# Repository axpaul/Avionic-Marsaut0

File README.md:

# Avionic Marsaut 0

> *© 2021 Paul Miailhe, all rights reserved.*  
> *Material licensed under [→ CC BY-NC-SA 4.0](https://creativecommons.org/licenses/by-nc-sa/4.0)*

## Experimental Rocket Avionics for Marsaut 0

The **Marsaut 0 avionics system**, designed and developed by Paul Miailhe in 2021, was successfully launched during the C'Space event. This project is licensed under **CC BY-NC-SA 4.0**.

The avionics system is based on an **STM32F303K8** microcontroller, which provides high-performance real-time control for the rocket's systems. It integrates essential sensors, motor drivers, and interface boards to ensure a robust and reliable solution for experimental rocketry.

You can access the CAD designs for all the boards [here on GrabCAD](https://grabcad.com/library/avionics-system-for-marsaut-0-rocket-mines-space-1).

---

## System Overview

The electronic architecture of the rocket is divided into the following branches:

---

- **Branch APU** (Acquisition Process Unit):  
  Responsible for acquiring, storing, and transmitting data, equipped with:  
  - **MPU6050**: A 6-axis gyroscope and accelerometer for attitude measurement.  
  - **BMP280**: A barometric pressure sensor for altitude estimation.

---

- **Branch SEQ** (Flight Controller):  
  The core control board, based on the **STM32F303K8**, which manages actuators and flight status monitoring.

---

- **Branch ALIM** (Power Supply):  
  Handles power distribution and monitors the battery's state of charge.

---

- **Branch MOTOR**:  
  Includes two **VNH5019 motor drivers** (by STMicroelectronics) for controlling the parachute deployment system.

---

- **Branch LINK**:  
  Connects all actuators and sensors in the rocket to the avionics for seamless operation.

---

- **Branch HMI** (Human-Machine Interface):  
  Provides a user interface for controlling the system and displaying key information.

---

- **Branch INT_LTS**:  
  Serves as the interface for integrating the **LoRa TTGO-T BEAM** communication module.

---

## Key Components

### **Microcontroller**
- **STM32F303K8**:  
  - ARM Cortex-M3 core with floating-point unit (FPU).  
  - Provides real-time control and data processing capabilities.

### **Sensors**
- **MPU6050**:  
  - A 6-axis IMU for measuring acceleration and angular velocity.  
  - Enables precise attitude and motion tracking.
- **BMP280**:  
  - A barometric pressure sensor for accurate altitude estimation.

### **Motor Drivers**
- **VNH5019** (by STMicroelectronics):  
  - High-power motor drivers capable of handling currents up to 12A.  
  - Used to control the parachute deployment mechanism with precision.

---

## Features and Applications

- **Real-time Control**:  
  The STM32F303K8 ensures smooth operation of actuators and sensors.  

- **Integrated Sensors**:  
  MPU6050 and BMP280 provide reliable data for navigation and altitude tracking.

- **High-Performance Motor Control**:  
  The VNH5019 motor drivers ensure precise parachute deployment and safety.

- **Seamless Communication**:  
  LoRa TTGO-T BEAM module enables efficient data transmission to ground stations.

---

## Visual Overview

### Avionics System CAD
You can find the full CAD designs of the avionics system on [GrabCAD](https://grabcad.com/library/avionics-system-for-marsaut-0-rocket-mines-space-1).

### Images

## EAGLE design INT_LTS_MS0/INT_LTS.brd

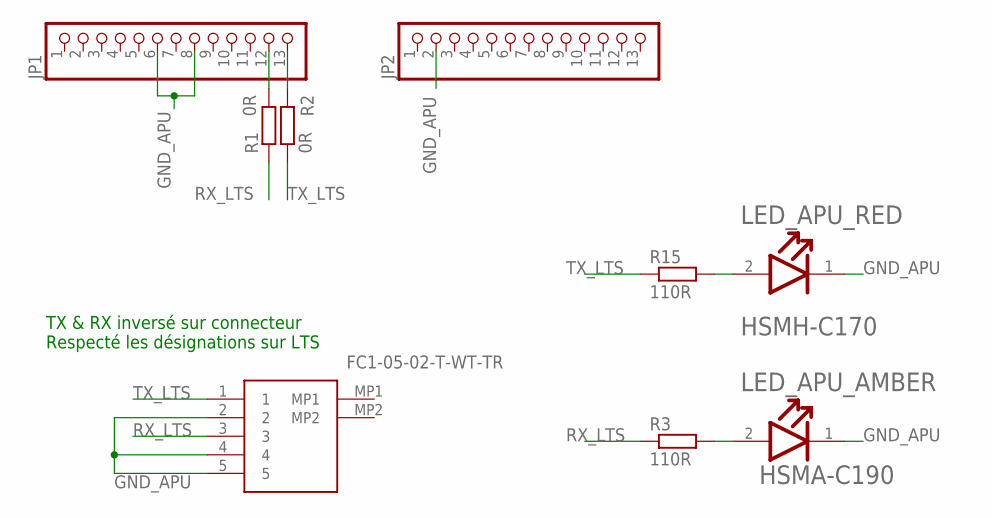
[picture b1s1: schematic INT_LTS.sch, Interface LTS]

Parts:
J7: FC1-05-02-T-WT-TR; FC10502TWTTR
JP1, JP2: PINHD-1X13; 1X13
LED_APU_AMBER: BROADCOM_HSMA-C190BROADCOM_HSMA-C190_0_0; BROADCOM_HSMA-C190_0
LED_APU_RED: BROADCOM_HSMH-C170BROADCOM_HSMH-C170_0_0; BROADCOM_HSMH-C170_0
R1, R2: 0R; R0603
R3, R15: 110R; R0603

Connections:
GND_APU: J7.2, J7.4, J7.5, JP1.6, JP1.8, JP2.2, LED_APU_AMBER.1 (CATHODE), LED_APU_RED.1 (CATHODE)
unnamed: JP1.12, R1.2
unnamed: JP1.13, R2.2
unnamed: LED_APU_AMBER.2 (ANODE), R3.2
unnamed: LED_APU_RED.2 (ANODE), R15.2
RX_LTS: J7.3, R1.1, R3.1
TX_LTS: J7.1, R2.1, R15.1

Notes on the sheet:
TX & RX inversé sur connecteur Respecté les désignations sur LTS

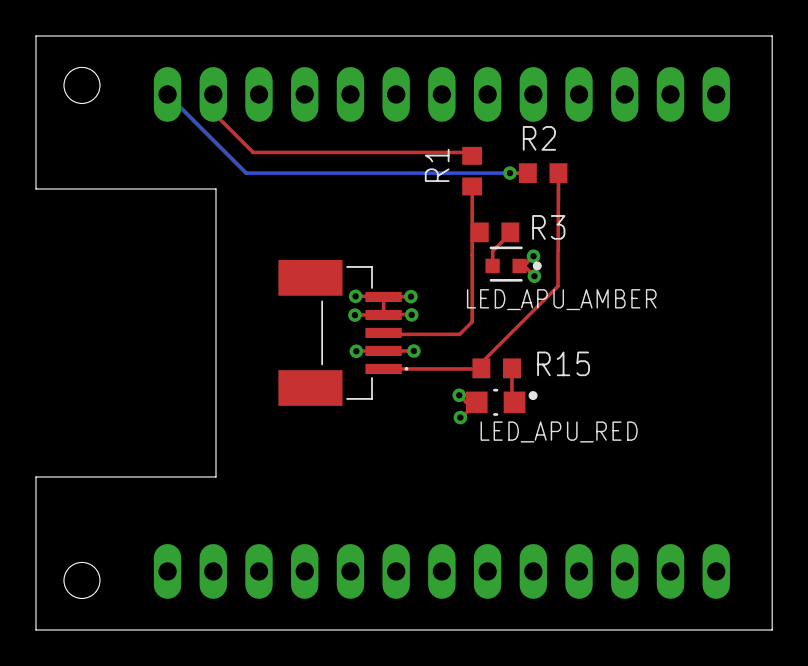
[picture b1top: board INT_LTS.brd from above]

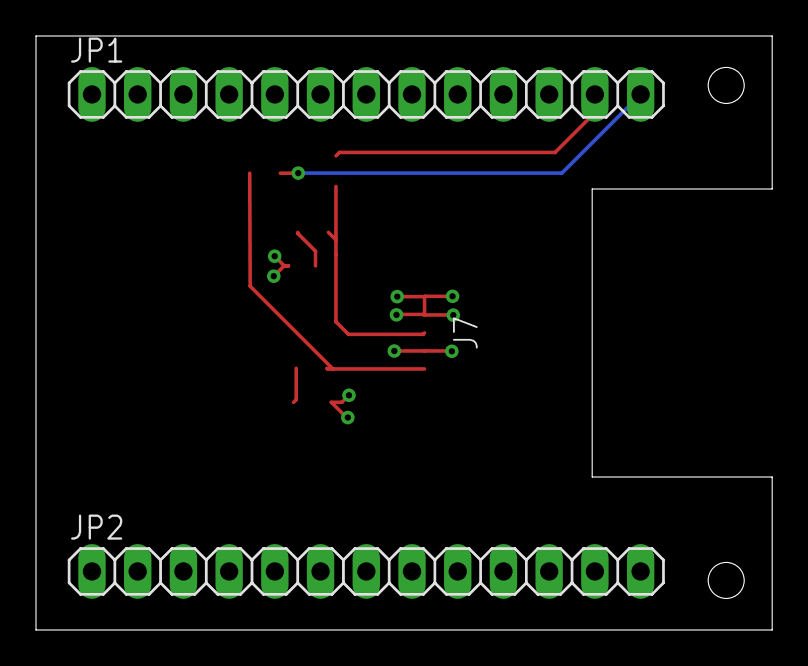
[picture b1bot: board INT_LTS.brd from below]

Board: 2 copper layers, 40.9 x 33.0 mm, 9 parts (2 on the bottom side), 7 nets.

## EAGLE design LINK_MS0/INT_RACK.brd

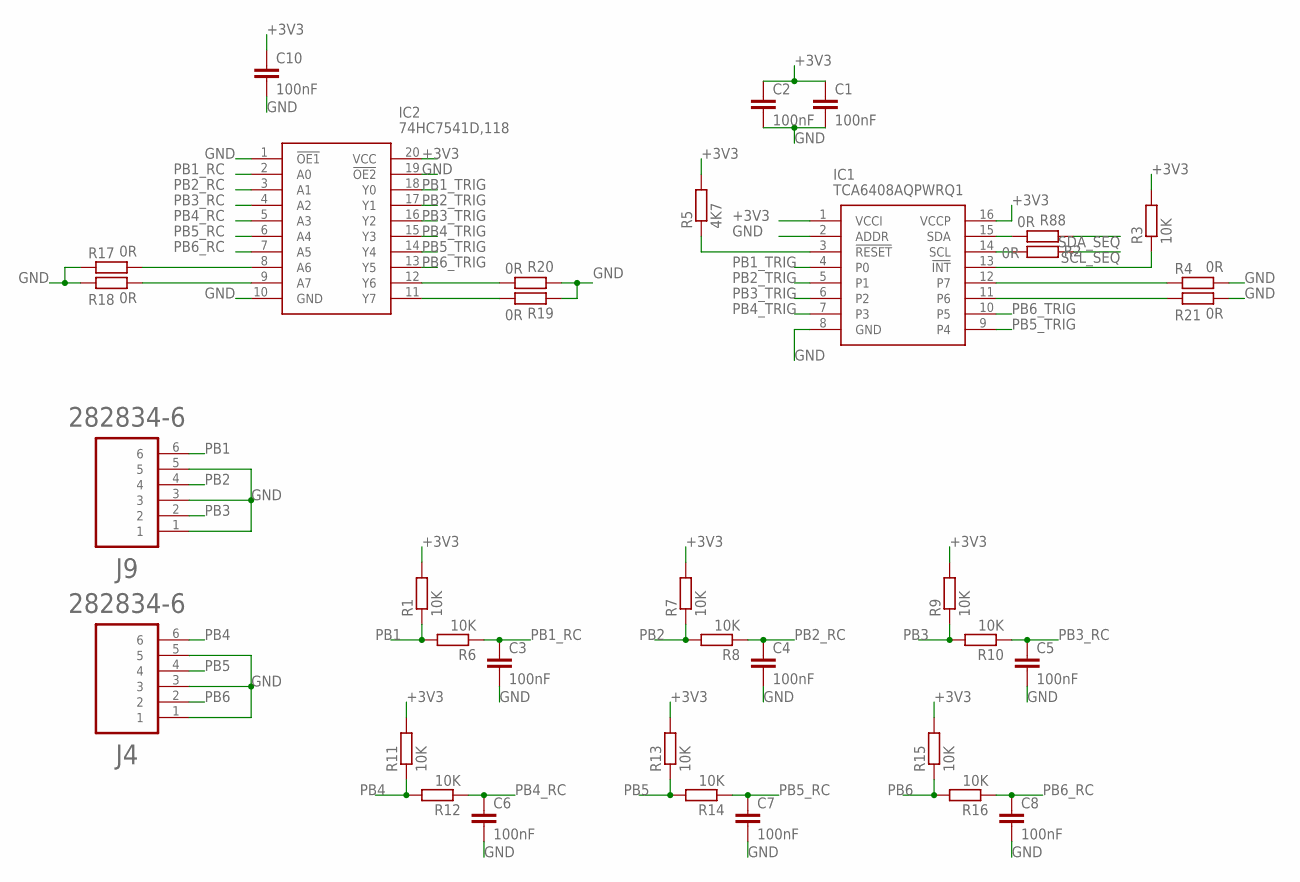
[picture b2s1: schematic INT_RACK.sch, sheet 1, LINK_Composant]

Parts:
C1, C2, C3, C4, C5, C6, C7, C8, C10: 100nF; C0805
IC1: TCA6408AQPWRQ1; SOP65P640X120-16N
IC2: 74HC7541D,118; SOIC127P1032X265-20N
J4, J9: 282834-6; TE_282834-6
R1, R3, R6, R7, R8, R9, R10, R11, R12, R13, R14, R15, R16: 10K; R0603
R2, R4, R17, R18, R19, R20, R21, R88: 0R; R0603
R5: 4K7; R0603

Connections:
+3V3: C1.1, C2.1, C10.1, IC1.1 (VCCI), IC1.16 (VCCP), IC2.20 (VCC), R1.2, R3.2, R5.2, R7.2, R9.2, R11.2, R13.2, R15.2; also elsewhere on the board
GND: C1.2, C2.2, C3.2, C4.2, C5.2, C6.2, C7.2, C8.2, C10.2, IC1.2 (ADDR), IC1.8 (GND), IC2.1 (!OE1), IC2.10 (GND), IC2.19 (!OE2), J4.1, J4.3, J4.5, J9.1, J9.3, J9.5, R4.2, R17.1, R18.1, R19.1, R20.1, R21.2; also elsewhere on the board
unnamed: IC1.11 (P6), R21.1
unnamed: IC1.14 (SCL), R2.2
unnamed: IC1.13 (!INT), R3.1
unnamed: IC1.12 (P7), R4.1
unnamed: IC1.3 (!RESET), R5.1
unnamed: IC2.12 (Y6), R20.2
unnamed: IC2.11 (Y7), R19.2
unnamed: IC2.8 (A6), R17.2
unnamed: IC2.9 (A7), R18.2
unnamed: IC1.15 (SDA), R88.2
PB1: J9.6, R1.1, R6.2
PB1_RC: C3.1, IC2.2 (A0), R6.1
PB1_TRIG: IC1.4 (P0), IC2.18 (Y0)
PB2: J9.4, R7.1, R8.2
PB2_RC: C4.1, IC2.3 (A1), R8.1
PB2_TRIG: IC1.5 (P1), IC2.17 (Y1)
PB3: J9.2, R9.1, R10.2
PB3_RC: C5.1, IC2.4 (A2), R10.1
PB3_TRIG: IC1.6 (P2), IC2.16 (Y2)
PB4: J4.6, R11.1, R12.2
PB4_RC: C6.1, IC2.5 (A3), R12.1
PB4_TRIG: IC1.7 (P3), IC2.15 (Y3)
PB5: J4.4, R13.1, R14.2
PB5_RC: C7.1, IC2.6 (A4), R14.1
PB5_TRIG: IC1.9 (P4), IC2.14 (Y4)
PB6: J4.2, R15.1, R16.2
PB6_RC: C8.1, IC2.7 (A5), R16.1
PB6_TRIG: IC1.10 (P5), IC2.13 (Y5)
SCL_SEQ: R2.1; also elsewhere on the board
SDA_SEQ: R88.1; also elsewhere on the board

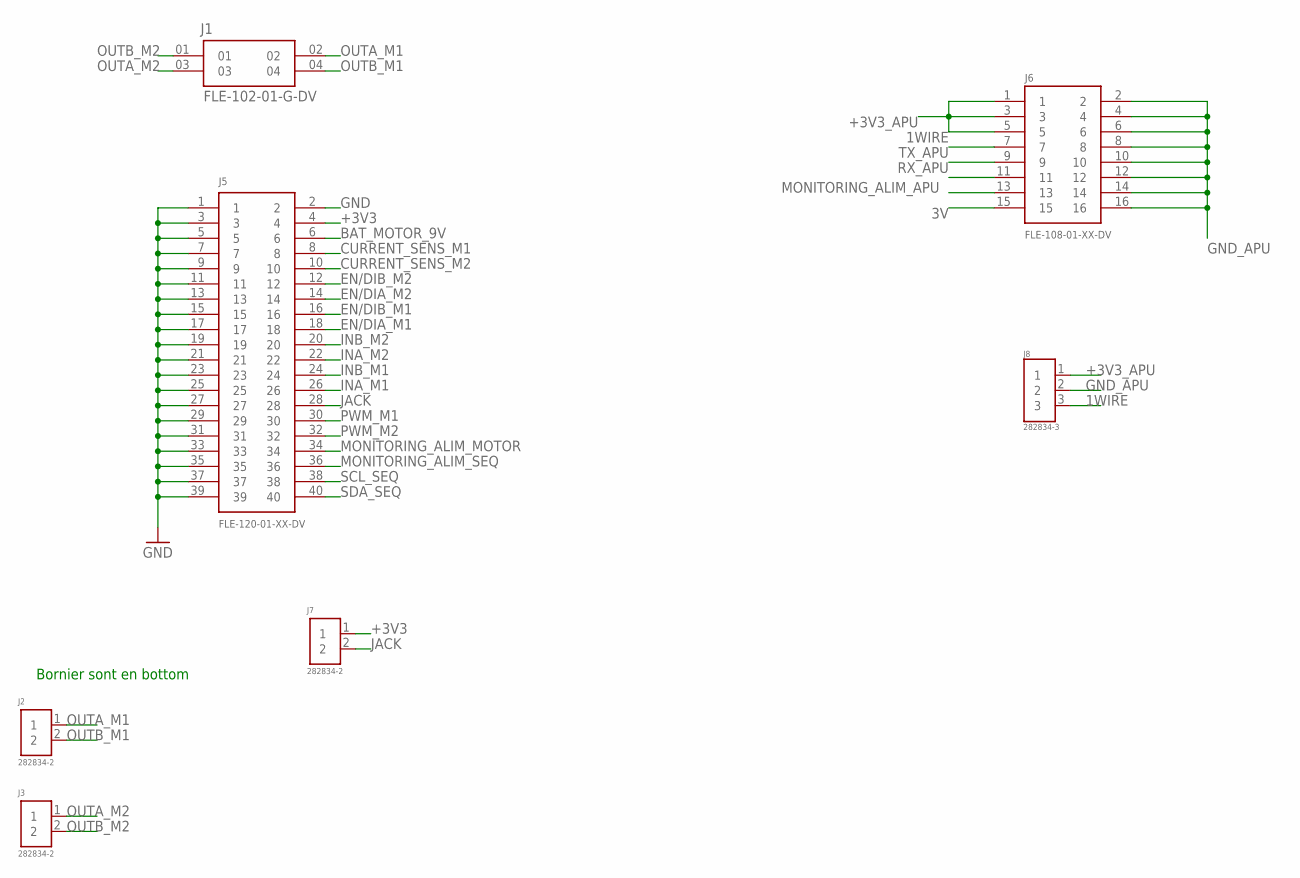
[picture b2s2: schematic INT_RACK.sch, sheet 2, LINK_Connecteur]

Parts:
J1: FLE-102-01-G-DV; SAMTEC_FLE-102-01-G-DV
J2, J3, J7: 282834-2; CONN_282834-2
J5: FLE-120-01-XX-DV
J6: FLE-108-01-XX-DV
J8: 282834-3; TE_282834-3

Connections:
1WIRE: J6.7, J8.3
3V: J6.15
+3V3: J5.4, J7.1; also elsewhere on the board
+3V3_APU: J6.1, J6.3, J6.5, J8.1
BAT_MOTOR_9V: J5.6
CURRENT_SENS_M1: J5.8
CURRENT_SENS_M2: J5.10
EN/DIA_M1: J5.18
EN/DIA_M2: J5.14
EN/DIB_M1: J5.16
EN/DIB_M2: J5.12
GND: J5.1, J5.2, J5.3, J5.5, J5.7, J5.9, J5.11, J5.13, J5.15, J5.17, J5.19, J5.21, J5.23, J5.25, J5.27, J5.29, J5.31, J5.33, J5.35, J5.37, J5.39; also elsewhere on the board
GND_APU: J6.2, J6.4, J6.6, J6.8, J6.10, J6.12, J6.14, J6.16, J8.2
INA_M1: J5.26
INA_M2: J5.22
INB_M1: J5.24
INB_M2: J5.20
JACK: J5.28, J7.2
MONITORING_ALIM_APU: J6.13
MONITORING_ALIM_MOTOR: J5.34
MONITORING_ALIM_SEQ: J5.36
OUTA_M1: J1.02, J2.1
OUTA_M2: J1.03, J3.1
OUTB_M1: J1.04, J2.2
OUTB_M2: J1.01, J3.2
PWM_M1: J5.30
PWM_M2: J5.32
RX_APU: J6.11
SCL_SEQ: J5.38; also elsewhere on the board
SDA_SEQ: J5.40; also elsewhere on the board
TX_APU: J6.9

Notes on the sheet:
Bornier sont en bottom

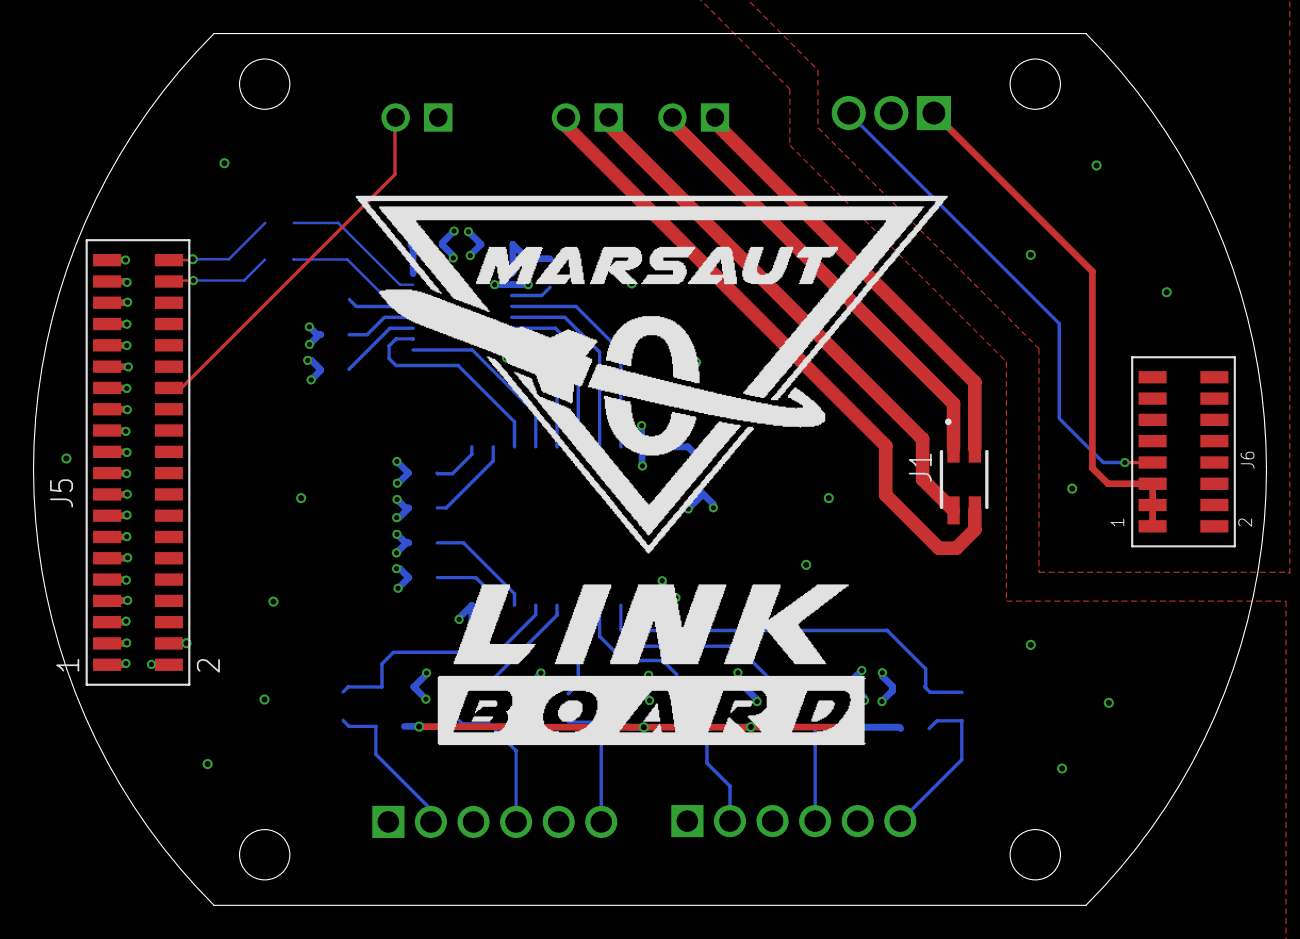
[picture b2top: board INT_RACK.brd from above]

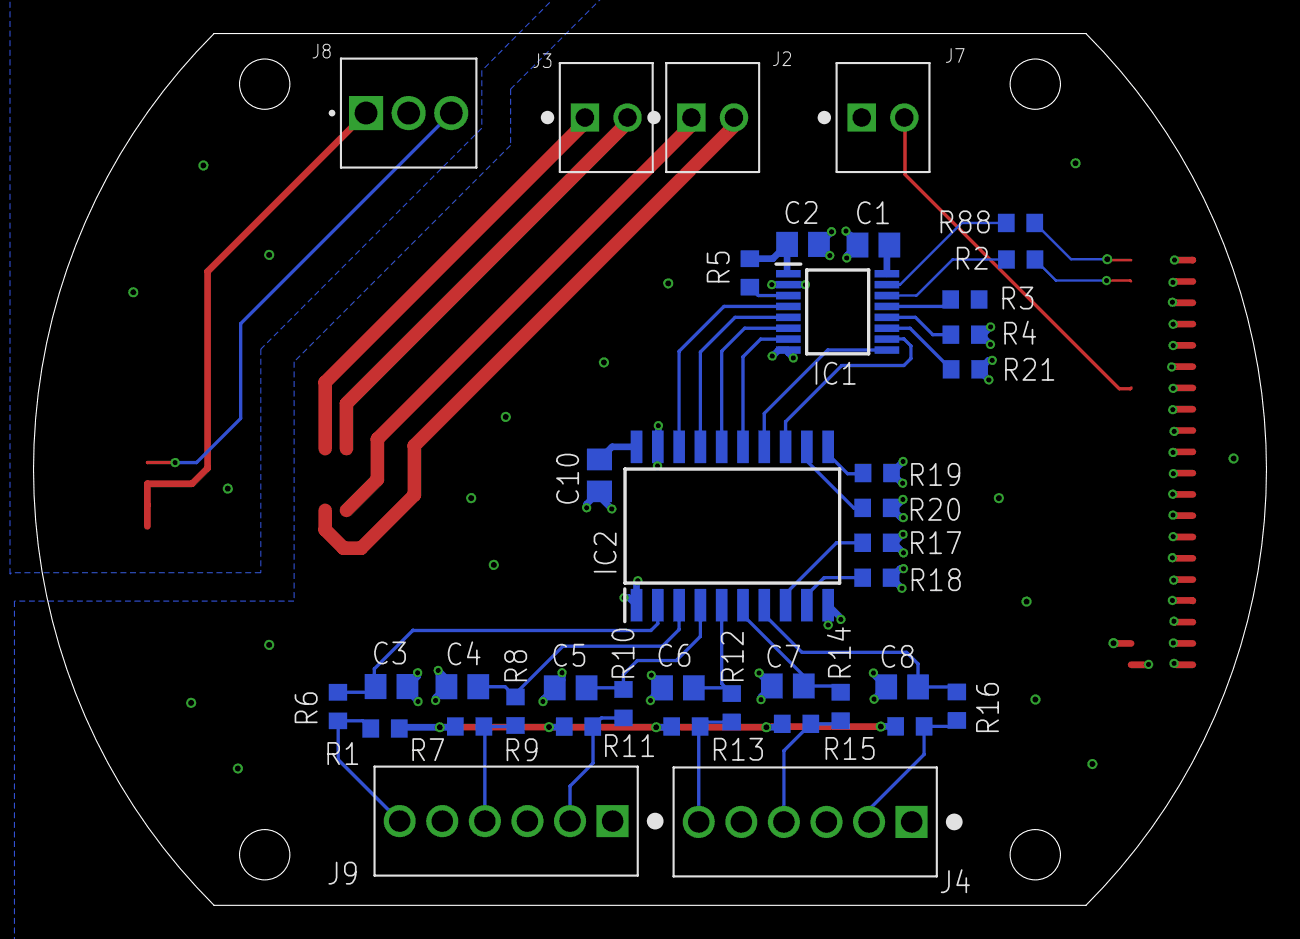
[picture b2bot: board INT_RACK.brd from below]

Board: 4 copper layers, 73.5 x 52.0 mm, 42 parts (39 on the bottom side), 40 nets.

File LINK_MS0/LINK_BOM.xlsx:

Qty | Value | MPN | Package | Parts | Description | LCSC Part
8 | 0R | 0603WAF0000T5E | R0603 | R2, R4, R17, R18, R19, R20, R21, R88 | RESISTOR, European symbol | C21189
9 | 100nF | CC0805KRX7R9BB104 | C0805 | C1, C2, C3, C4, C5, C6, C7, C8, C10 | CAPACITOR, European symbol | C49678
13 | 10K | 0603WAF1002T5E | R0603 | R1, R3, R6, R7, R8, R9, R10, R11, R12, R13, R14, R15, R16 | RESISTOR, European symbol | C25804
3 | 282834-2 | NON-CONNECTED | CONN_282834-2 | J2, J3, J7 | Terminal block; 2.54mm; angled 90Â°; 0.03Ã·1mm2; ways: 2; 10A; H: 10mm Check pr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
1 | 282834-3 | NON-CONNECTED | TE_282834-3 | J8 | Conn; Term Blk; PCB; Wire Receptacle; 3; 2.54mm; 30-16AWG; Green; 10A; 150V; M1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
2 | 282834-6 | NON-CONNECTED | TE_282834-6 | J4, J9 | TERM BLOCK 6POS SIDE ENT 2.54MM Check prices
1 | 4K7 | 0603WAF4701T5E | R0603 | R5 | RESISTOR, European symbol | C23162
1 | 74HC7541D,118 | NON-CONNECTED | SOIC127P1032X265-20N | IC2 | 74HC(T)7541 - Octal Schmitt trigger buffer/line driver; 3-state@en-us
1 | FLE-102-01-G-DV | NON-CONNECTED | SAMTEC_FLE-102-01-G-DV | J1 | Check prices
1 | FLE-108-01-XX-DV | NON-CONNECTED | FLE-108-01-XX-DV | J6 | DOUBLE ROW 0.050X0.050" STRIP ASSEMBLY. Check prices"
1 | FLE-120-01-XX-DV | NON-CONNECTED | FLE-120-01-XX-DV | J5 | DOUBLE ROW 0.050X0.050" STRIP ASSEMBLY. Check prices"
1 | TCA6408AQPWRQ1 | NON-CONNECTED | SOP65P640X120-16N | IC1 | Automotive Low-Voltage 8-Bit I2C and SMBus I/O Expander With Interrupt Output

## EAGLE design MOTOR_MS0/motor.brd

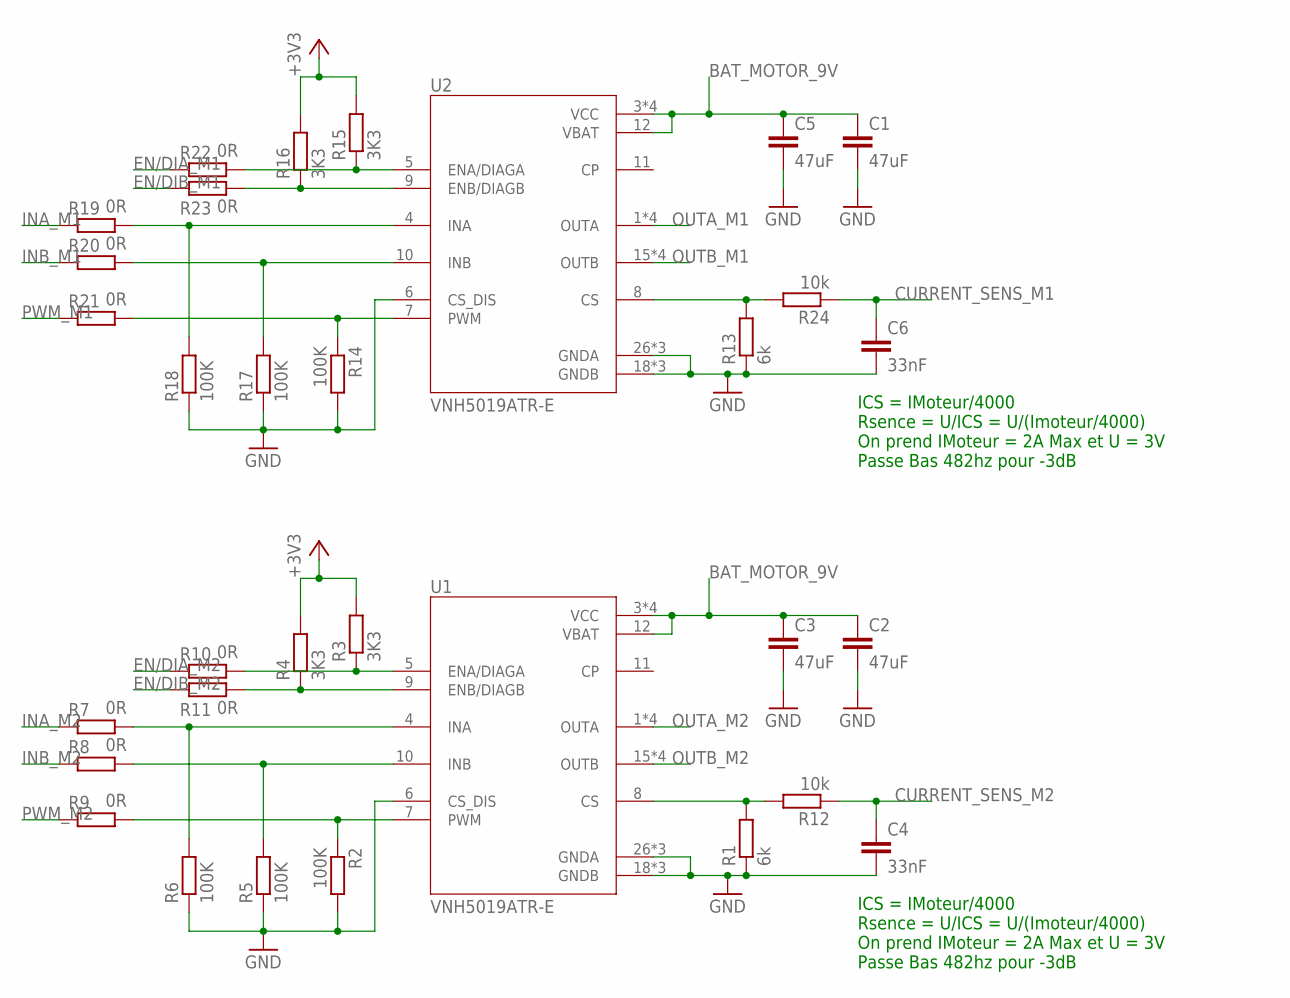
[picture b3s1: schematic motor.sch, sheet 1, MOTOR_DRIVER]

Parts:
C1, C2, C3, C5: 47uF; C0805
C4, C6: 33nF; C0805
R1, R13: 6k; R0603
R2, R5, R6, R14, R17, R18: 100K; R0603
R3, R4, R15, R16: 3K3; R0603
R7, R8, R9, R10, R11, R19, R20, R21, R22, R23: 0R; R0603
R12, R24: 10k; R0603
U1, U2: VNH5019ATR-E; IC_VNH5019ATR-E

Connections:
+3V3: R3.2, R4.2, R15.2, R16.2; also elsewhere on the board
BAT_MOTOR_9V: C1.1, C2.1, C3.1, C5.1, U1.3 (VCC), U1.12 (VBAT), U1.13 (VCC), U1.23 (VCC), U1.HS1 (VCC), U2.3 (VCC), U2.12 (VBAT), U2.13 (VCC), U2.23 (VCC), U2.HS1 (VCC); also elsewhere on the board
CURRENT_SENS_M1: C6.1, R24.1; also elsewhere on the board
CURRENT_SENS_M2: C4.1, R12.1; also elsewhere on the board
EN/DIA_M1: R22.1; also elsewhere on the board
EN/DIA_M2: R10.1; also elsewhere on the board
EN/DIB_M1: R23.1; also elsewhere on the board
EN/DIB_M2: R11.1; also elsewhere on the board
GND: C1.2, C2.2, C3.2, C4.2, C5.2, C6.2, R1.1, R2.2, R5.1, R6.1, R13.1, R14.2, R17.1, R18.1, U1.6 (CS_DIS), U1.18 (GNDB), U1.19 (GNDB), U1.20 (GNDB), U1.26 (GNDA), U1.27 (GNDA), U1.28 (GNDA), U2.6 (CS_DIS), U2.18 (GNDB), U2.19 (GNDB), U2.20 (GNDB), U2.26 (GNDA), U2.27 (GNDA), U2.28 (GNDA); also elsewhere on the board
INA_M1: R19.1; also elsewhere on the board
INA_M2: R7.1; also elsewhere on the board
INB_M1: R20.1; also elsewhere on the board
INB_M2: R8.1; also elsewhere on the board
unnamed: R1.2, R12.2, U1.8 (CS)
unnamed: R3.1, R10.2, U1.5 (ENA/DIAGA)
unnamed: R4.1, R11.2, U1.9 (ENB/DIAGB)
unnamed: R2.1, R9.2, U1.7 (PWM)
unnamed: R5.2, R8.2, U1.10 (INB)
unnamed: R6.2, R7.2, U1.4 (INA)
unnamed: R13.2, R24.2, U2.8 (CS)
unnamed: R15.1, R22.2, U2.5 (ENA/DIAGA)
unnamed: R16.1, R23.2, U2.9 (ENB/DIAGB)
unnamed: R14.1, R21.2, U2.7 (PWM)
unnamed: R17.2, R20.2, U2.10 (INB)
unnamed: R18.2, R19.2, U2.4 (INA)
OUTA_M1: U2.1 (OUTA), U2.25 (OUTA), U2.30 (OUTA), U2.HS2 (OUTA); also elsewhere on the board
OUTA_M2: U1.1 (OUTA), U1.25 (OUTA), U1.30 (OUTA), U1.HS2 (OUTA); also elsewhere on the board
OUTB_M1: U2.15 (OUTB), U2.16 (OUTB), U2.21 (OUTB), U2.HS3 (OUTB); also elsewhere on the board
OUTB_M2: U1.15 (OUTB), U1.16 (OUTB), U1.21 (OUTB), U1.HS3 (OUTB); also elsewhere on the board
PWM_M1: R21.1; also elsewhere on the board
PWM_M2: R9.1; also elsewhere on the board

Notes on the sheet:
ICS = IMoteur/4000 Rsence = U/ICS = U/(Imoteur/4000) On prend IMoteur = 2A Max et U = 3V Passe Bas 482hz pour -3dB

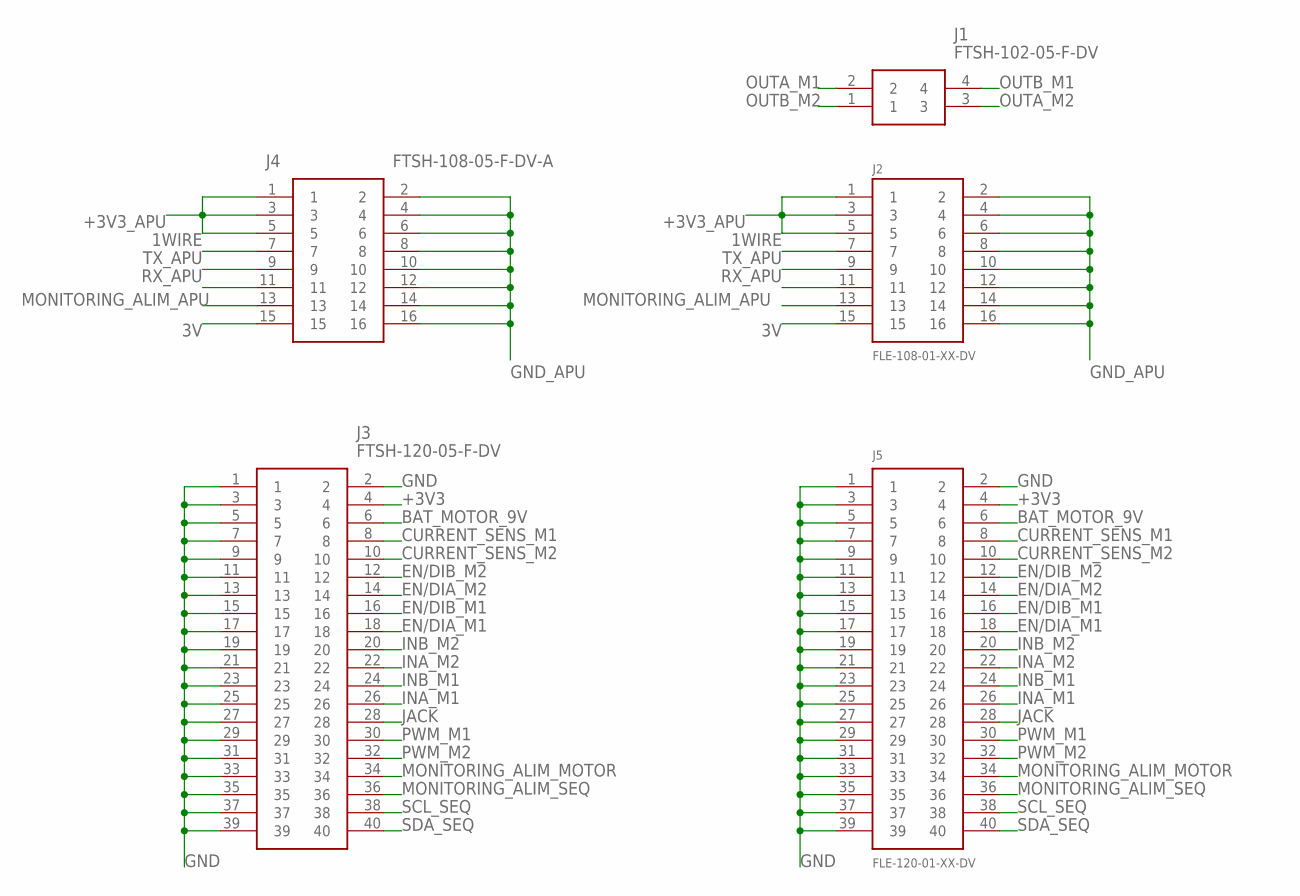
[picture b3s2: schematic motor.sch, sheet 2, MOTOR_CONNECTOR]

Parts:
J1: FTSH-102-05-F-DV; FTSH-102-XX-YYY-DV
J2: FLE-108-01-XX-DV
J3: FTSH-120-05-F-DV; FTSH-120-XX-YYY-DV
J4: FTSH-108-05-F-DV-A; FTSH-108-XX-YYY-DV-A
J5: FLE-120-01-XX-DV

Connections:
1WIRE: J2.7, J4.7
3V: J2.15, J4.15
+3V3: J3.4, J5.4; also elsewhere on the board
+3V3_APU: J2.1, J2.3, J2.5, J4.1, J4.3, J4.5
BAT_MOTOR_9V: J3.6, J5.6; also elsewhere on the board
CURRENT_SENS_M1: J3.8, J5.8; also elsewhere on the board
CURRENT_SENS_M2: J3.10, J5.10; also elsewhere on the board
EN/DIA_M1: J3.18, J5.18; also elsewhere on the board
EN/DIA_M2: J3.14, J5.14; also elsewhere on the board
EN/DIB_M1: J3.16, J5.16; also elsewhere on the board
EN/DIB_M2: J3.12, J5.12; also elsewhere on the board
GND: J3.1, J3.2, J3.3, J3.5, J3.7, J3.9, J3.11, J3.13, J3.15, J3.17, J3.19, J3.21, J3.23, J3.25, J3.27, J3.29, J3.31, J3.33, J3.35, J3.37, J3.39, J5.1, J5.2, J5.3, J5.5, J5.7, J5.9, J5.11, J5.13, J5.15, J5.17, J5.19, J5.21, J5.23, J5.25, J5.27, J5.29, J5.31, J5.33, J5.35, J5.37, J5.39; also elsewhere on the board
GND_APU: J2.2, J2.4, J2.6, J2.8, J2.10, J2.12, J2.14, J2.16, J4.2, J4.4, J4.6, J4.8, J4.10, J4.12, J4.14, J4.16
INA_M1: J3.26, J5.26; also elsewhere on the board
INA_M2: J3.22, J5.22; also elsewhere on the board
INB_M1: J3.24, J5.24; also elsewhere on the board
INB_M2: J3.20, J5.20; also elsewhere on the board
JACK: J3.28, J5.28
MONITORING_ALIM_APU: J2.13, J4.13
MONITORING_ALIM_MOTOR: J3.34, J5.34
MONITORING_ALIM_SEQ: J3.36, J5.36
OUTA_M1: J1.2; also elsewhere on the board
OUTA_M2: J1.3; also elsewhere on the board
OUTB_M1: J1.4; also elsewhere on the board
OUTB_M2: J1.1; also elsewhere on the board
PWM_M1: J3.30, J5.30; also elsewhere on the board
PWM_M2: J3.32, J5.32; also elsewhere on the board
RX_APU: J2.11, J4.11
SCL_SEQ: J3.38, J5.38
SDA_SEQ: J3.40, J5.40
TX_APU: J2.9, J4.9

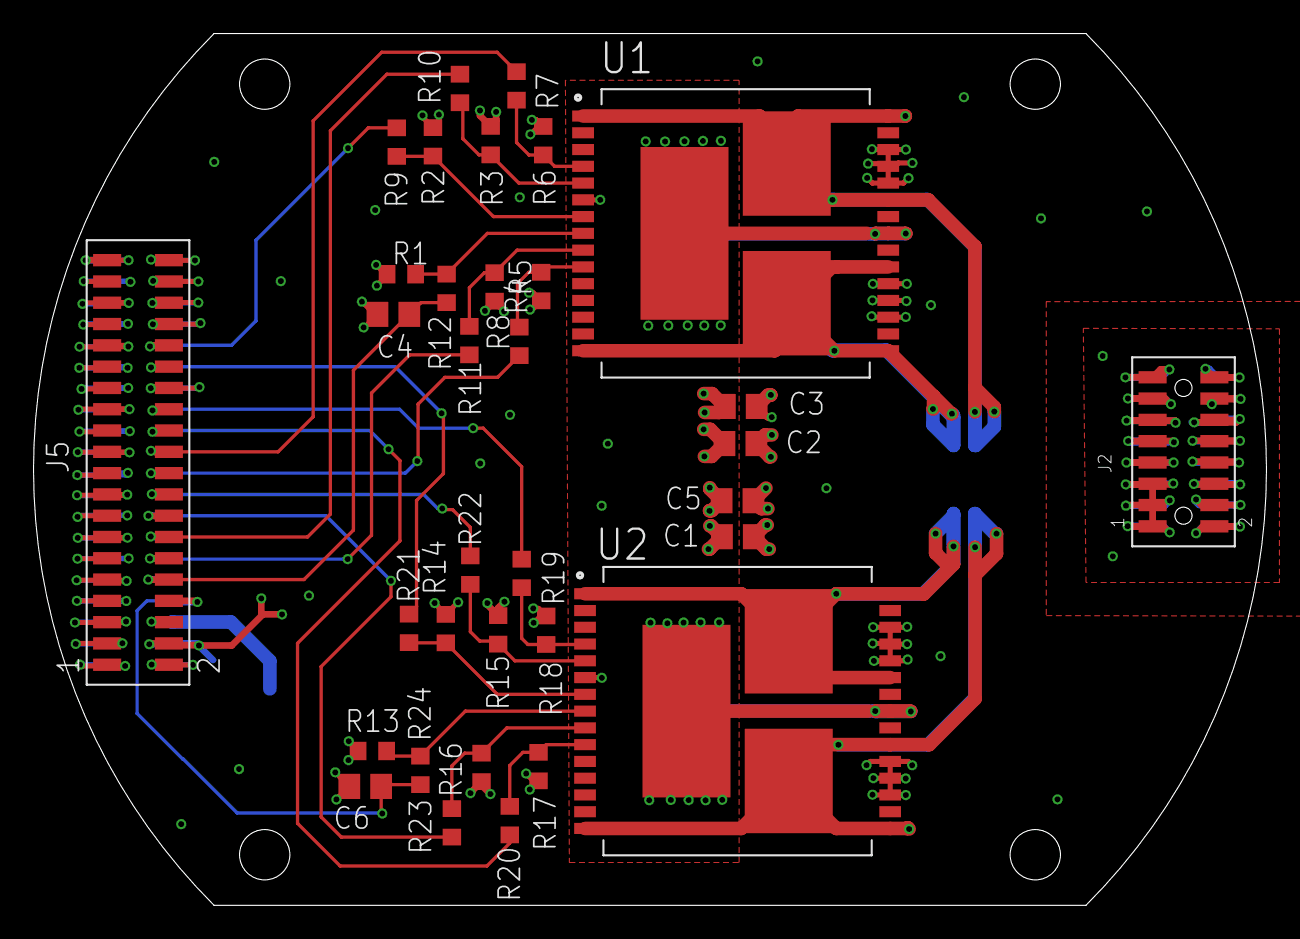
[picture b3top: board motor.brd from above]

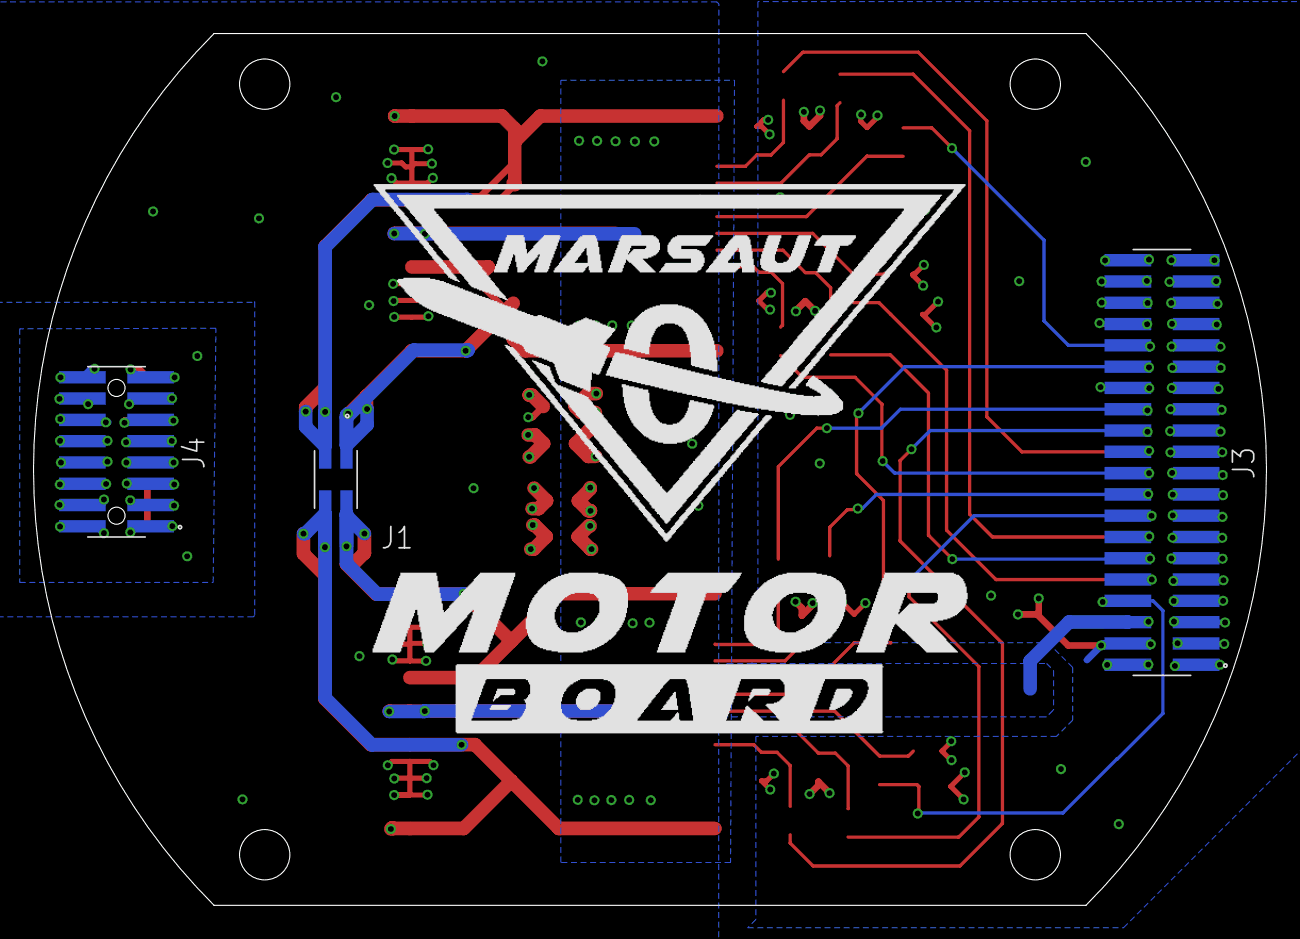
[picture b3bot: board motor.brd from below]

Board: 4 copper layers, 73.5 x 52.0 mm, 37 parts (3 on the bottom side), 43 nets.

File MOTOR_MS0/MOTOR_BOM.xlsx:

Qty | Value | MPN | Package | Parts | Description | LCSC Part
10 | 0R | 0603WAF0000T5E | R0603 | R7, R8, R9, R10, R11, R19, R20, R21, R22, R23 | RESISTOR, European symbol | C21189
6 | 100K | 0603WAF1003T5E | R0603 | R2, R5, R6, R14, R17, R18 | RESISTOR, European symbol | C25803
2 | 10k | 0603WAF1002T5E | R0603 | R12, R24 | RESISTOR, European symbol | C25804
2 | 33nF | 0805B333K500NT | C0805 | C4, C6 | CAPACITOR, European symbol | C1739
4 | 3K3 | 0603WAF3301T5E | R0603 | R3, R4, R15, R16 | RESISTOR, European symbol | C22978
4 | 22uF | CL21A226MAQNNNE | C0805 | C1, C2, C3, C5 | CAPACITOR, European symbol | C45783
2 | 5K6 | 0603WAF5601T5E | R0603 | R1, R13 | RESISTOR, European symbol | C23189
1 | FLE-108-01-XX-DV | NON-CONNECTED | FLE-108-01-XX-DV | J2 | DOUBLE ROW 0.050X0.050" STRIP ASSEMBLY. Check prices"
1 | FLE-120-01-XX-DV | NON-CONNECTED | FLE-120-01-XX-DV | J5 | DOUBLE ROW 0.050X0.050" STRIP ASSEMBLY. Check prices"
1 | FTSH-102-05-F-DV | NON-CONNECTED | FTSH-102-XX-YYY-DV | J1 | 4 Position, High Reliability Header Strips, 0.050 pitch"
1 | FTSH-108-05-F-DV-A | NON-CONNECTED | FTSH-108-XX-YYY-DV-A | J4 | 16 Position, High Reliability Header Strips, 0.050 pitch"
1 | FTSH-120-05-F-DV | NON-CONNECTED | FTSH-120-XX-YYY-DV | J3 | 40 Position, High Reliability Header Strips, 0.050 pitch"
2 | VNH5019ATR-E | NON-CONNECTED | IC_VNH5019ATR-E | U1, U2 | Motor / Motion / Ignition Controllers & Drivers Automotive h-Bridge 18mohm 30a 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

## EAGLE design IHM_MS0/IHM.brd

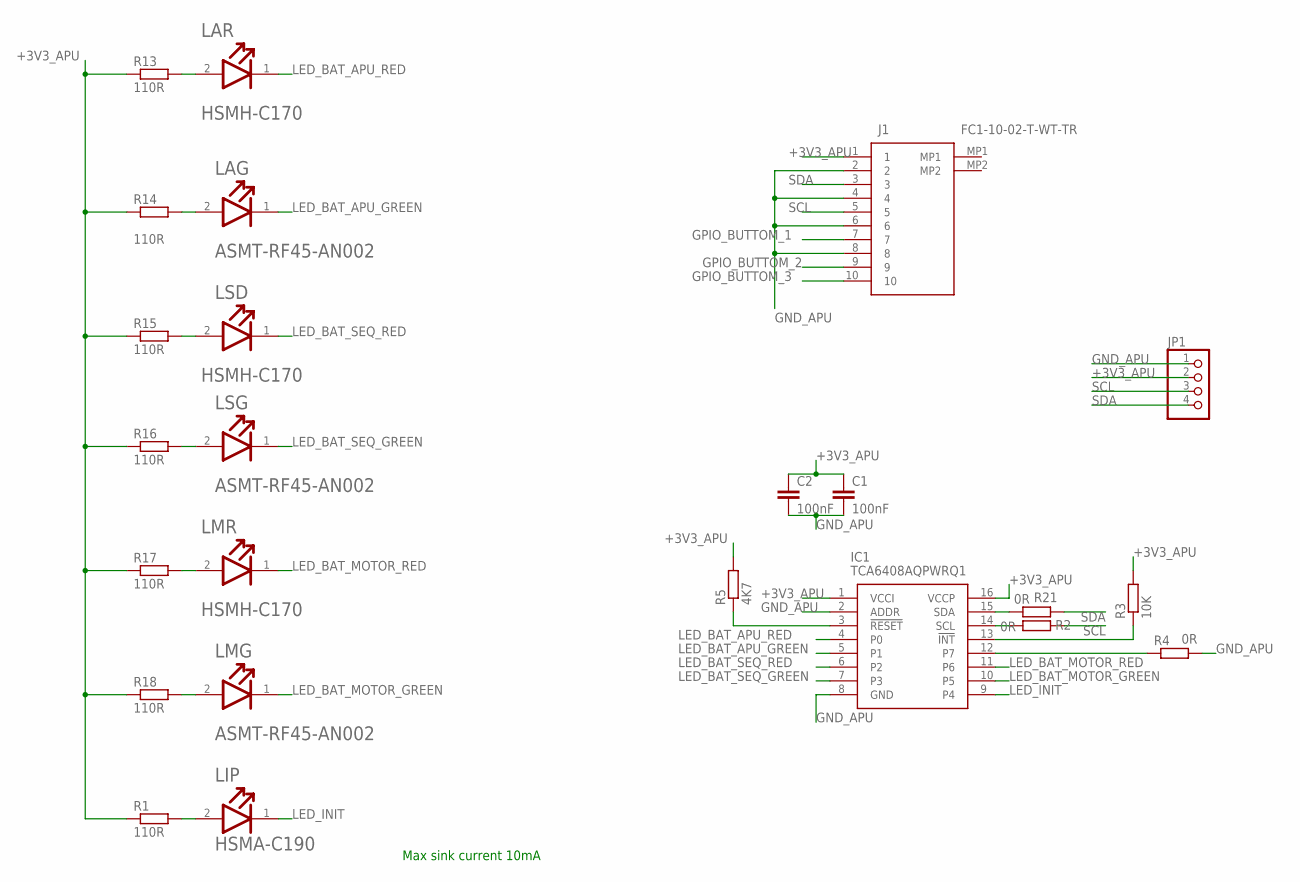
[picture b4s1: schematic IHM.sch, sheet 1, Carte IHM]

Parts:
C1, C2: 100nF; C0805
IC1: TCA6408AQPWRQ1; SOP65P640X120-16N
J1: FC1-10-02-T-WT-TR; FC11002TWTTR
JP1: PINHD-1X4; 1X04
LAG: BROADCOM_ASMT-RF45-AN002BROADCOM_ASMT-RF45-AN002_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; BROADCOM_ASMT-RF45-AN002_0
LAR: BROADCOM_HSMH-C170BROADCOM_HSMH-C170_0_0; BROADCOM_HSMH-C170_0
LIP: BROADCOM_HSMA-C190BROADCOM_HSMA-C190_0_0; BROADCOM_HSMA-C190_0
LMG: BROADCOM_ASMT-RF45-AN002BROADCOM_ASMT-RF45-AN002_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; BROADCOM_ASMT-RF45-AN002_0
LMR: BROADCOM_HSMH-C170BROADCOM_HSMH-C170_0_0; BROADCOM_HSMH-C170_0
LSD: BROADCOM_HSMH-C170BROADCOM_HSMH-C170_0_0; BROADCOM_HSMH-C170_0
LSG: BROADCOM_ASMT-RF45-AN002BROADCOM_ASMT-RF45-AN002_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; BROADCOM_ASMT-RF45-AN002_0
R1, R13, R14, R15, R16, R17, R18: 110R; R0603
R2, R4, R21: 0R; R0603
R3: 10K; R0603
R5: 4K7; R0603

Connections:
+3V3_APU: C1.1, C2.1, IC1.1 (VCCI), IC1.16 (VCCP), J1.1, JP1.2, R1.1, R3.2, R5.2, R13.1, R14.1, R15.1, R16.1, R17.1, R18.1; also elsewhere on the board
GND_APU: C1.2, C2.2, IC1.2 (ADDR), IC1.8 (GND), J1.2, J1.4, J1.6, J1.8, JP1.1, R4.2; also elsewhere on the board
GPIO_BUTTOM_1: J1.7; also elsewhere on the board
GPIO_BUTTOM_2: J1.9; also elsewhere on the board
GPIO_BUTTOM_3: J1.10; also elsewhere on the board
LED_BAT_APU_GREEN: IC1.5 (P1), LAG.1 (CATHODE)
LED_BAT_APU_RED: IC1.4 (P0), LAR.1 (CATHODE)
LED_BAT_MOTOR_GREEN: IC1.10 (P5), LMG.1 (CATHODE)
LED_BAT_MOTOR_RED: IC1.11 (P6), LMR.1 (CATHODE)
LED_BAT_SEQ_GREEN: IC1.7 (P3), LSG.1 (CATHODE)
LED_BAT_SEQ_RED: IC1.6 (P2), LSD.1 (CATHODE)
LED_INIT: IC1.9 (P4), LIP.1 (CATHODE)
unnamed: LIP.2 (ANODE), R1.2
unnamed: IC1.14 (SCL), R2.2
unnamed: IC1.13 (!INT), R3.1
unnamed: IC1.12 (P7), R4.1
unnamed: IC1.3 (!RESET), R5.1
unnamed: LAR.2 (ANODE), R13.2
unnamed: LAG.2 (ANODE), R14.2
unnamed: LSD.2 (ANODE), R15.2
unnamed: LSG.2 (ANODE), R16.2
unnamed: IC1.15 (SDA), R21.2
unnamed: LMR.2 (ANODE), R17.2
unnamed: LMG.2 (ANODE), R18.2
SCL: J1.5, JP1.3, R2.1
SDA: J1.3, JP1.4, R21.1

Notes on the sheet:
Max sink current 10mA

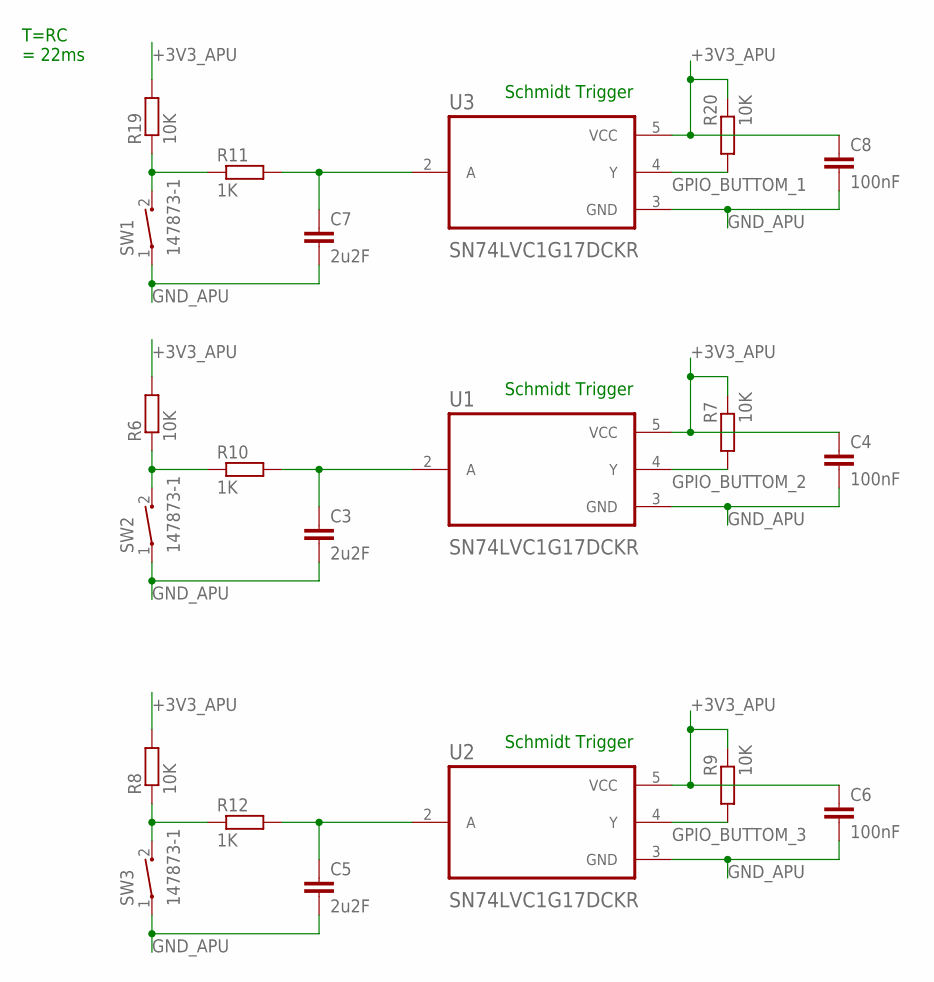
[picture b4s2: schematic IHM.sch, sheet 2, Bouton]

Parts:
C3, C5, C7: 2u2F; C0805K
C4, C6, C8: 100nF; C0805K
R6, R7, R8, R9, R19, R20: 10K; R0603
R10, R11, R12: 1K; R0603
SW1, SW2, SW3: 147873-1; SW_147873-1
U1, U2, U3: SN74LVC1G17DCKR; SOT65P210X110-5N

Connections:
+3V3_APU: C4.1, C6.1, C8.1, R6.2, R7.2, R8.2, R9.2, R19.2, R20.2, U1.5 (VCC), U2.5 (VCC), U3.5 (VCC); also elsewhere on the board
GND_APU: C3.2, C4.2, C5.2, C6.2, C7.2, C8.2, SW1.1, SW2.1, SW3.1, U1.3 (GND), U2.3 (GND), U3.3 (GND); also elsewhere on the board
GPIO_BUTTOM_1: R20.1, U3.4 (Y); also elsewhere on the board
GPIO_BUTTOM_2: R7.1, U1.4 (Y); also elsewhere on the board
GPIO_BUTTOM_3: R9.1, U2.4 (Y); also elsewhere on the board
unnamed: C3.1, R10.2, U1.2 (A)
unnamed: R6.1, R10.1, SW2.2
unnamed: C5.1, R12.2, U2.2 (A)
unnamed: R8.1, R12.1, SW3.2
unnamed: C7.1, R11.2, U3.2 (A)
unnamed: R11.1, R19.1, SW1.2

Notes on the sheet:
Schmidt Trigger
T=RC = 22ms

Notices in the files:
README.md:
https://github.com/axpaul/Avionic-Marsaut0/blob/main/Pictures/Cc-by-nc-sa_icon.svg.png
